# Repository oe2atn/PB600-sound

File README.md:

<p align="center"><b>🇬🇧 English</b> &nbsp;|&nbsp; <a href="README.de.md">🇩🇪 Deutsch</a></p>

# PB600 Sound

Engine sound module for the **1:7 RC PistenBully 600**, built for the **4x3D Universal Receiver** with Xbox controller.
A small carrier board plugs onto an ESP32 DevKit and plays start, idle, rev-up, shutdown, horn and reversing beep.
Volumes and engine behaviour are set in the browser over USB, no software needed.

Everything is free for anyone who wants to build the board themselves: PCB data for JLCPCB, enclosure, firmware and setup page.

**Step-by-step guide:** [English](docs/GUIDE.md) · [Deutsch](docs/ANLEITUNG.md)

> [!CAUTION]
> **Check the polarity of the power plug (J5)!** Ready-made JST-PH leads often have **red and black swapped**.
> Red must go to **+**, black to **−** as marked on the board. Measure before plugging in and swap the contacts in the plug if needed.
> On the first module a lead with swapped colours went up in smoke.

## Features

- carrier board 28.5 × 52 mm, all parts between the ESP32 header rows, assembled by JLCPCB
- input 7 to 18 V (2S to 4S LiPo), reverse polarity protection
- class D amplifier for a 4 to 8 Ω speaker
- 2 PWM inputs: sound throttle (CH7) and horn / engine on-off (CH13)
- engine revs with the throttle and drops back quickly; reversing beep only while reversing
- setup page in Chrome / Edge: volumes, max rpm, rev up / rev down, throttle end points, firmware update
- screwed 3D-printed enclosure with two-colour lettering

## Repository

| Folder | Content |
|---|---|
| [`docs/`](docs) | step-by-step guide (EN / DE), controller cheat sheets, pictures |
| [`hardware/`](hardware) | KiCad project, Gerber, BOM and CPL for JLCPCB, schematic, data sheet |
| [`enclosure/`](enclosure) | STL, 3MF and OpenSCAD source of the enclosure |
| [`firmware/`](firmware) | PlatformIO source and ready-made binaries (version 1.7) |
| [`web-setup/`](web-setup) | setup page (Web Serial, German / English) |

## Quick start

1. Order the board from JLCPCB with the files in [`hardware/production/`](hardware/production). **Check part rotations in the 3D preview.**
2. Print the enclosure from [`enclosure/`](enclosure).
3. Flash the ESP32 on the **[setup page](https://oe2atn.github.io/PB600-sound/web-setup/?lang=en)** (Chrome / Edge, "Full install").
4. Wire it: J5 power (**mind the polarity!**), J6 speaker, J3 ← receiver CH7, J4 ← receiver CH13.
5. Set up CH7 and CH13 in the 4x3D receiver.
6. LiPo off → USB → connect on the setup page → LiPo on → press Menu → calibrate throttle → set volumes → save.

Details for every step: [docs/GUIDE.md](docs/GUIDE.md).

## Controller mapping

Suggested button mapping for the sound on the Xbox controller (4x3D receiver, Snowcat Config V1.3):

German version: [`docs/img/PB600-Sound-Controller-DE.png`](docs/img/PB600-Sound-Controller-DE.png). Full channel map of the PB600 and cheat sheet: [`docs/controller/`](docs/controller).

## Connectors you need

| On the board | Plug | Wire to |
|---|---|---|
| J5 IN 7-18V | **JST-PH 2.0 mm, 2 pin** (PHR-2) | battery, 2S to 4S. **Red = +, black = −** |
| J6 SPEAKER | **JST-PH 2.0 mm, 2 pin** (PHR-2) | speaker 4 to 8 Ω, never to ground |
| J3 THR | servo lead 2.54 mm | receiver channel 7, signal only |
| J4 FN | servo lead 2.54 mm | receiver channel 13, signal only |

## Credits and licences

- Firmware based on [Rc_Engine_Sound_ESP32](https://github.com/TheDIYGuy999/Rc_Engine_Sound_ESP32) by **TheDIYGuy999**. Please respect the terms of the upstream project.
- PistenBully sound files: from the PistenBully sound set, publicly available from **dasmikro via AliExpress** and obtained there.
- Flashing in the browser: [esptool-js](https://github.com/espressif/esptool-js) by Espressif, Apache 2.0.
- Hardware, enclosure, setup page and documentation: **CC BY-NC-SA 4.0**, see [LICENSE.md](LICENSE.md). Free to build and modify for private use; no commercial use.

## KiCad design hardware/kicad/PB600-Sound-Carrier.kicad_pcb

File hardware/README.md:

# PB600 Sound Carrier, rev 1.3

Plug-on board for an ESP32 DevKit (30 pin), 28.5 × 52 mm, 2 layers. All parts sit between the header rows.

| File | Content |
|---|---|
| `production/PB600-Gerber.zip` | Gerber files for JLCPCB |
| `production/BOM_JLCPCB.csv` | bill of materials with LCSC part numbers |
| `production/CPL_JLCPCB.csv` | pick and place |
| `kicad/` | KiCad 7 project (schematic and layout) |
| `PB600-Sound-Carrier-Schematic.pdf` | schematic |
| `PB600-Sound-Carrier-Datasheet.pdf` | one-page data sheet (enclosure dimensions there are for enclosure v1.0) |
| `PB600-Sound-Carrier-Overview.pdf` | connector overview (German) |

## Key data

- Input 7 to 18 V (2S to 4S LiPo), reverse polarity protection B5819W
- AP63205 buck converter, 5 V / 2 A for the ESP32
- PAM8403 class D amplifier, bridged mono output, approx. 1.5 W into 8 Ω
- 2 × PWM inputs (THR on GPIO14, FN on GPIO27), 4.7 kΩ series resistor and BAT54C clamp to 3.3 V
- Receiver power is not used (servo plus pin not connected)

## Connectors

| Ref | Function | Type | Mating plug |
|---|---|---|---|
| J5 | power in, 7 to 18 V | JST-PH 2.0 mm, 2 pin, side entry (S2B-PH-K) | JST PHR-2 with crimp contacts, or a ready-made JST-PH 2-pin lead |
| J6 | speaker 4 to 8 Ω | JST-PH 2.0 mm, 2 pin, side entry (S2B-PH-K) | JST PHR-2 |
| J3 | THR, throttle signal | servo header 2.54 mm, 3 pin, right angle | servo lead (JR/Futaba) |
| J4 | FN, function signal | servo header 2.54 mm, 3 pin, right angle | servo lead (JR/Futaba) |
| J1, J2 | ESP32 | female header 1 × 15, 2.54 mm | ESP32 DevKit 30 pin |

> [!CAUTION]
> **J5 polarity:** pin 1 is +, pin 2 is −, marked + and − on the board. Ready-made JST-PH leads often have red and black the other way round. Measure before plugging in and swap the contacts in the plug if needed.

## Ordering

See [the guide](../docs/GUIDE.md#2-ordering-the-board-from-jlcpcb) ([deutsch](../docs/ANLEITUNG.md#2-platine-bei-jlcpcb-bestellen)).
**Check the rotation of all parts in the JLCPCB 3D preview** before ordering.

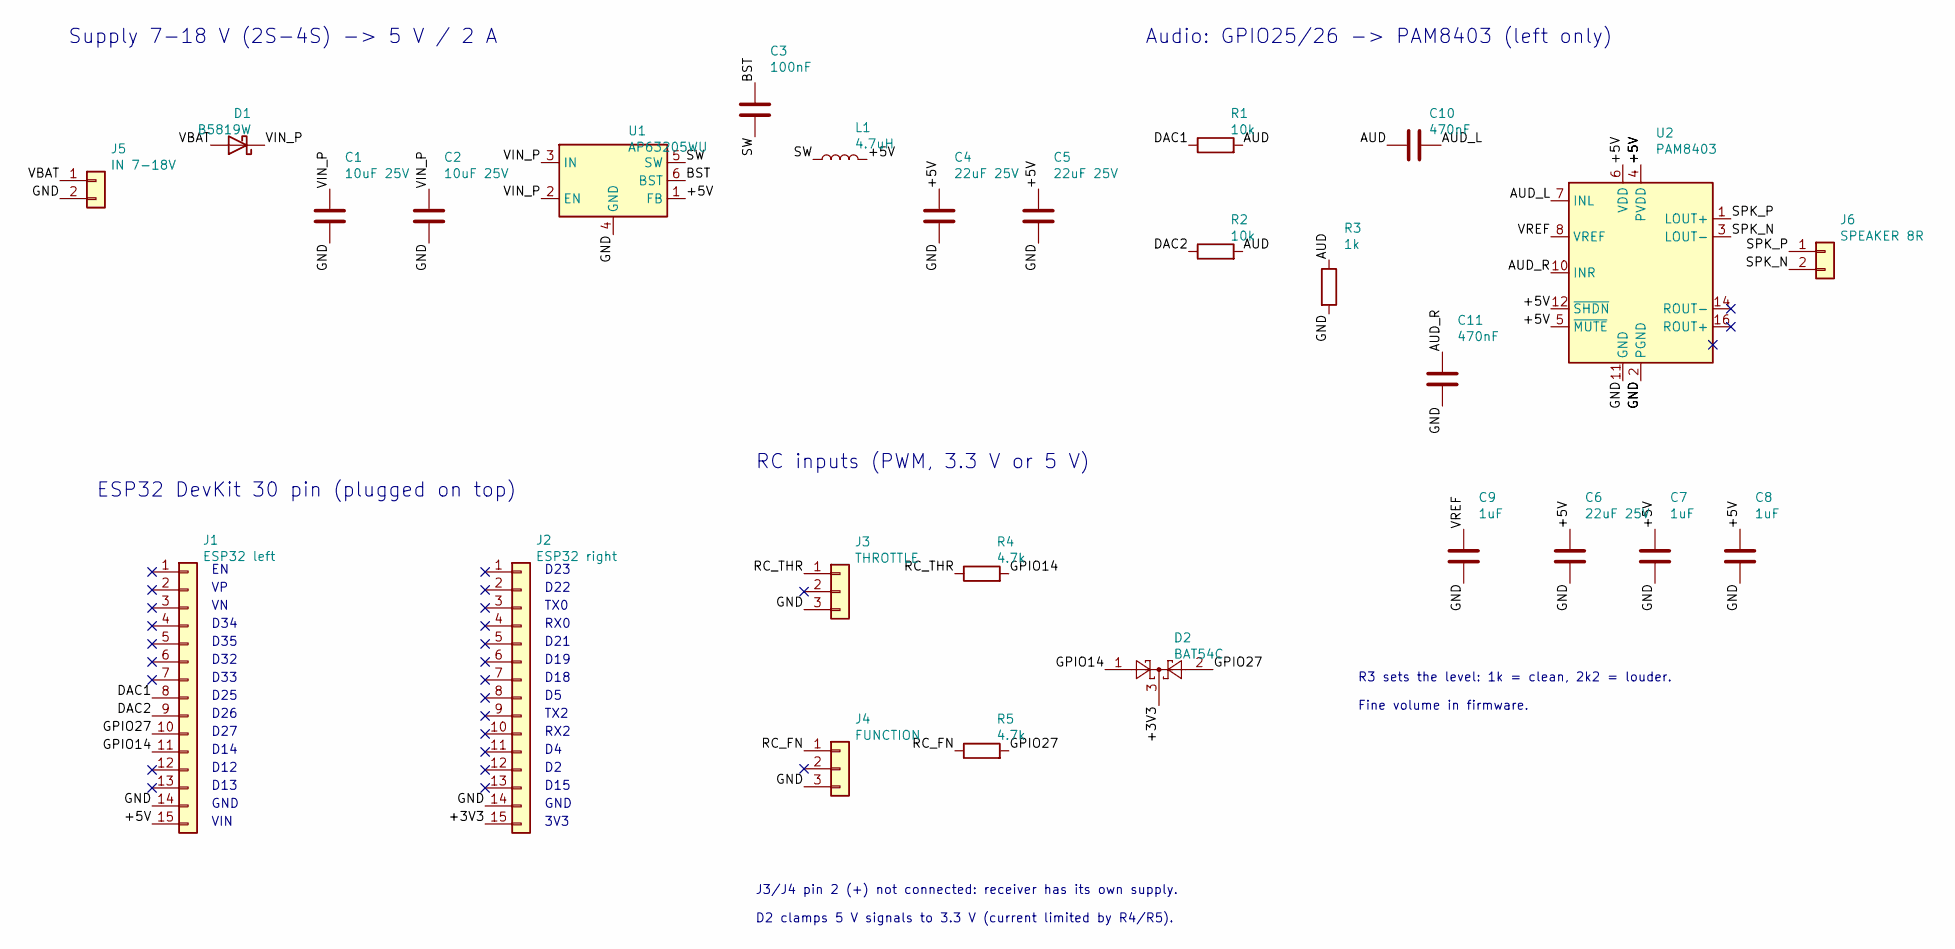
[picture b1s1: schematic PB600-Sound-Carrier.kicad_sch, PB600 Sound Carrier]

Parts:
C1, C2: 10uF 25V; C_0805_2012Metric; LCSC C15850
C3: 100nF; C_0603_1608Metric; LCSC C14663
C4, C5, C6: 22uF 25V; C_0805_2012Metric; LCSC C45783
C7, C8, C9: 1uF; C_0603_1608Metric; LCSC C15849
C10, C11: 470nF; C_0603_1608Metric; LCSC C1623
D1: B5819W; D_SOD-123; LCSC C8598
D2: BAT54C; SOT-23; LCSC C2135
J1: ESP32 left; PinSocket_1x15_P2.54mm_Vertical; LCSC C41417327
J2: ESP32 right; PinSocket_1x15_P2.54mm_Vertical; LCSC C41417327
J3: THROTTLE; PinHeader_1x03_P2.54mm_Horizontal; LCSC C32713262
J4: FUNCTION; PinHeader_1x03_P2.54mm_Horizontal; LCSC C32713262
J5: IN 7-18V; JST_PH_S2B-PH-K_1x02_P2.00mm_Horizontal; LCSC C173752
J6: SPEAKER 8R; JST_PH_S2B-PH-K_1x02_P2.00mm_Horizontal; LCSC C173752
L1: 4.7uH; L_Cenker_CKCS4030; LCSC C354587
R1, R2: 10k; R_0603_1608Metric; LCSC C25804
R3: 1k; R_0603_1608Metric; LCSC C21190
R4, R5: 4.7k; R_0603_1608Metric; LCSC C23162
U1: AP63205WU; TSOT-23-6; LCSC C2071056
U2: PAM8403; SOIC-16_3.9x9.9mm_P1.27mm; LCSC C17337

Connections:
+3V3: D2.3, J2.15
+5V: C4.1, C5.1, C6.1, C7.1, C8.1, J1.15, L1.2, U1.1 (FB), U2.4 (PVDD), U2.5 (~MUTE), U2.6 (VDD), U2.12 (~SHDN), U2.13 (PVDD)
AUD: C10.1, R1.2, R2.2, R3.1
AUD_L: C10.2, U2.7 (INL)
AUD_R: C11.1, U2.10 (INR)
BST: C3.1, U1.6 (BST)
DAC1: J1.8, R1.1
DAC2: J1.9, R2.1
GND: C1.2, C2.2, C4.2, C5.2, C6.2, C7.2, C8.2, C9.2, C11.2, J1.14, J2.14, J3.3, J4.3, J5.2, R3.2, U1.4 (GND), U2.2 (PGND), U2.11 (GND), U2.15 (PGND)
GPIO14: D2.1, J1.11, R4.2
GPIO27: D2.2, J1.10, R5.2
RC_FN: J4.1, R5.1
RC_THR: J3.1, R4.1
SPK_N: J6.2, U2.3 (LOUT-)
SPK_P: J6.1, U2.1 (LOUT+)
SW: C3.2, L1.1, U1.5 (SW)
VBAT: D1.2 (A), J5.1
VIN_P: C1.1, C2.1, D1.1 (K), U1.2 (EN), U1.3 (IN)
VREF: C9.1, U2.8 (VREF)

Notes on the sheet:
Supply 7-18 V (2S-4S) -> 5 V / 2 A
ESP32 DevKit 30 pin (plugged on top)
RC inputs (PWM, 3.3 V or 5 V)
Audio: GPIO25/26 -> PAM8403 (left only)
J3/J4 pin 2 (+) not connected: receiver has its own supply.
D2 clamps 5 V signals to 3.3 V (current limited by R4/R5).
R3 sets the level: 1k = clean, 2k2 = louder.
Fine volume in firmware.
D34
D35
D32
D33
D25
D26
D27
D14
D12
D13
GND
VIN
D23
D22
TX0
RX0
D21
D19
D18
TX2
RX2
D15
3V3

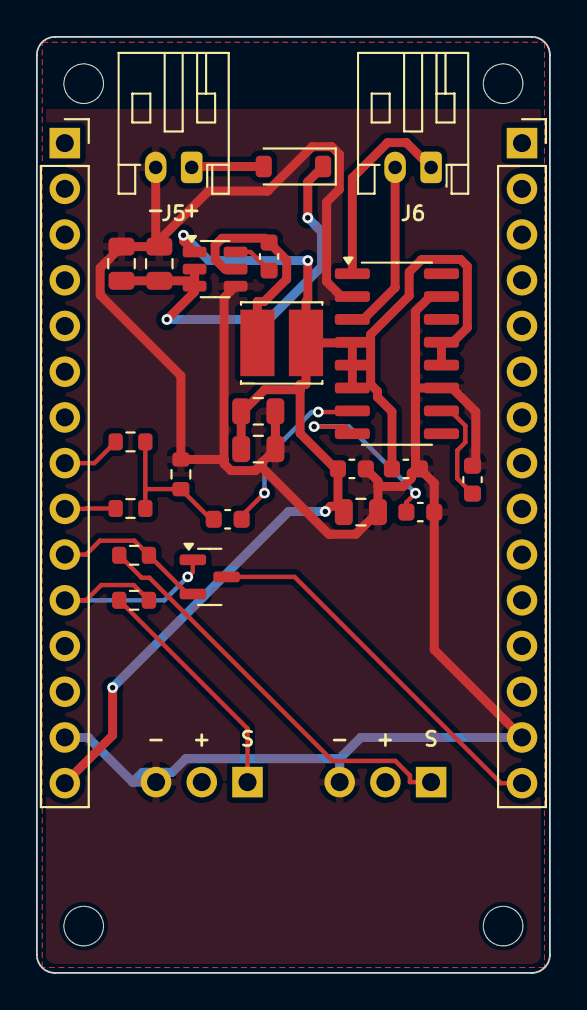
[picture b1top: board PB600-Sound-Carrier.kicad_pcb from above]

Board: 2 copper layers, 28.5 x 52.0 mm, 31 parts (0 on the bottom side), 19 nets.

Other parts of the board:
H1, H2, H3, H4: M2; MountingHole_2.2mm_M2

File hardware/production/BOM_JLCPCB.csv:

Comment,Designator,Footprint,LCSC Part #
10uF 25V,"C1,C2",C_0805_2012Metric,C15850
100nF,C3,C_0603_1608Metric,C14663
22uF 25V,"C4,C5,C6",C_0805_2012Metric,C45783
1uF,"C7,C8,C9",C_0603_1608Metric,C15849
470nF,"C10,C11",C_0603_1608Metric,C1623
B5819W,D1,D_SOD-123,C8598
BAT54C,D2,SOT-23,C2135
Female header 1x15 8.5mm,"J1,J2",PinSocket_1x15_P2.54mm_Vertical,C41417327
Pin header 1x3 right angle,"J3,J4",PinHeader_1x03_P2.54mm_Horizontal,C32713262
JST-PH 2P side entry,"J5,J6",JST_PH_S2B-PH-K_1x02_P2.00mm_Horizontal,C173752
4.7uH,L1,L_Cenker_CKCS4030,C354587
10k,"R1,R2",R_0603_1608Metric,C25804
1k,R3,R_0603_1608Metric,C21190
4.7k,"R4,R5",R_0603_1608Metric,C23162
AP63205WU,U1,TSOT-23-6,C2071056
PAM8403,U2,SOIC-16_3.9x9.9mm_P1.27mm,C17337
